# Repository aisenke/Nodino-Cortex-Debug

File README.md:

Nodino-Cortex-Debug
===================

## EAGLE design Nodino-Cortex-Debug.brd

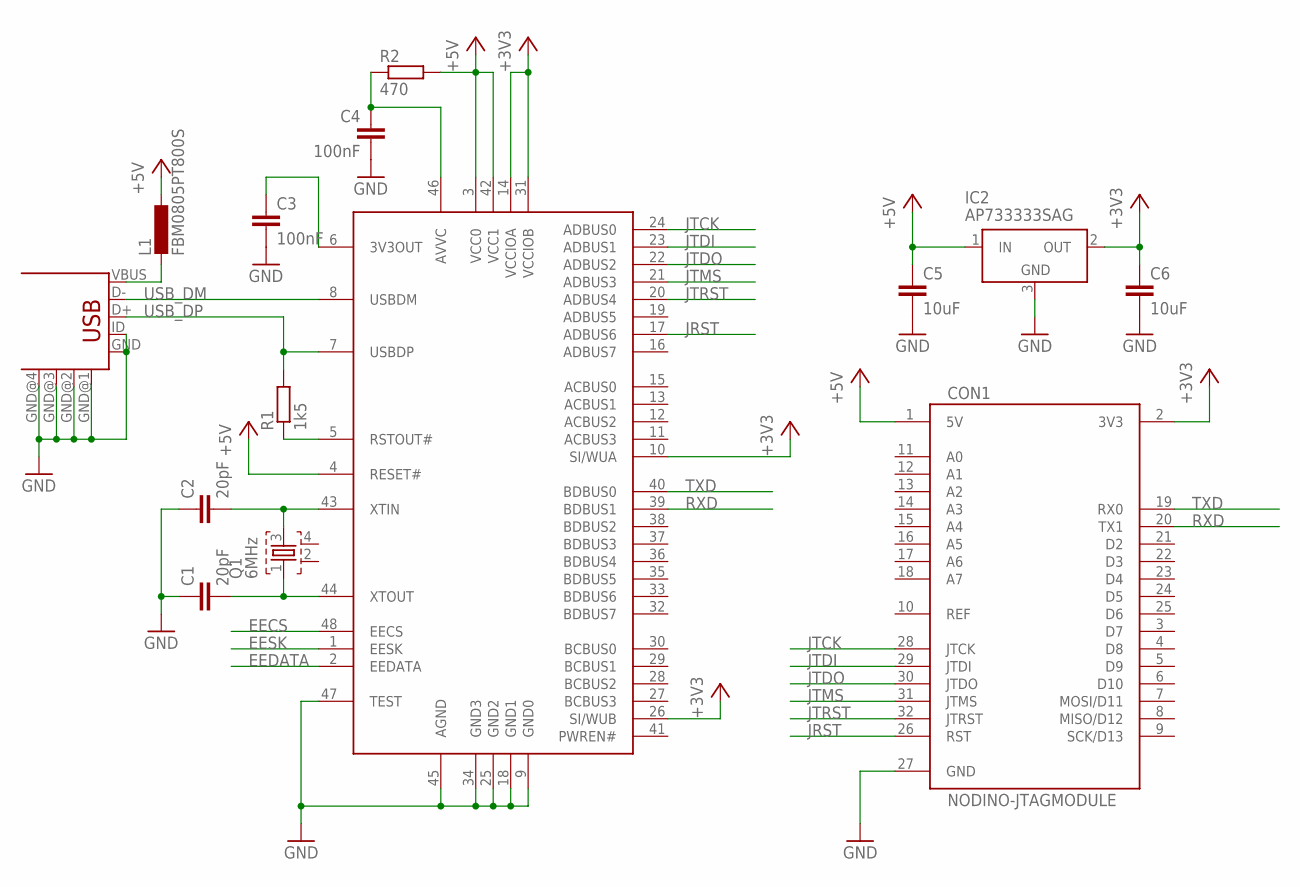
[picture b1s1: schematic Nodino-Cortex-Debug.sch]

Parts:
C1, C2: 20pF; C0603K
C3, C4: 100nF; C0603K
C5, C6: 10uF; C0603K
CON1: NODINO-JTAGMODULE; NODINO-JTAG-MOD
CON2: USB-OTG_SHIELD; USB-UAB-S1
IC1: FT2232D; LQFP48
IC2: AP733333SAG; SOT23
L1: FBM0805PT800S; L0805
Q1: 6MHz; FA-20H
R1: 1k5; R0603K
R2: 470; R0603K

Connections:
+3V3: C6.1, CON1.2 (3V3), IC1.10 (SI/WUA), IC1.14 (VCCIOA), IC1.26 (SI/WUB), IC1.31 (VCCIOB), IC2.2 (OUT)
+5V: C5.1, CON1.1 (5V), IC1.3 (VCC0), IC1.4 (RESET#), IC1.42 (VCC1), IC2.1 (IN), L1.1, R2.2
EECS: IC1.48 (EECS)
EEDATA: IC1.2 (EEDATA)
EESK: IC1.1 (EESK)
GND: C1.1, C2.1, C3.2, C4.2, C5.2, C6.2, CON1.27 (GND), CON2.GND, CON2.GND@1 (GND), CON2.GND@2 (GND), CON2.GND@3 (GND), CON2.GND@4 (GND), CON2.ID, IC1.9 (GND0), IC1.18 (GND1), IC1.25 (GND2), IC1.34 (GND3), IC1.45 (AGND), IC1.47 (TEST), IC2.3 (GND)
JRST: CON1.26 (RST), IC1.17 (ADBUS6)
JTCK: CON1.28 (JTCK), IC1.24 (ADBUS0)
JTDI: CON1.29 (JTDI), IC1.23 (ADBUS1)
JTDO: CON1.30 (JTDO), IC1.22 (ADBUS2)
JTMS: CON1.31 (JTMS), IC1.21 (ADBUS3)
JTRST: CON1.32 (JTRST), IC1.20 (ADBUS4)
unnamed: CON2.VBUS, L1.2
unnamed: IC1.5 (RSTOUT#), R1.1
unnamed: C4.1, IC1.46 (AVVC), R2.1
unnamed: C3.1, IC1.6 (3V3OUT)
unnamed: C1.2, IC1.44 (XTOUT), Q1.1
unnamed: C2.2, IC1.43 (XTIN), Q1.3
RXD: CON1.20 (TX1), IC1.39 (BDBUS1)
TXD: CON1.19 (RX0), IC1.40 (BDBUS0)
USB_DM: CON2.D-, IC1.8 (USBDM)
USB_DP: CON2.D+, IC1.7 (USBDP), R1.2

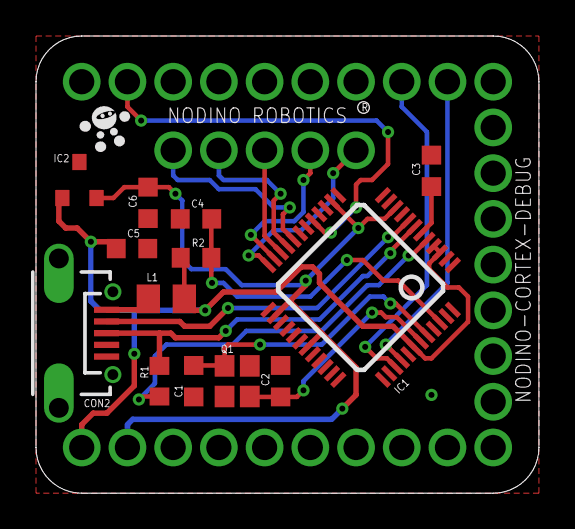
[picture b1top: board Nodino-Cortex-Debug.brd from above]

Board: 2 copper layers, 27.9 x 25.4 mm, 14 parts (0 on the bottom side), 19 nets.

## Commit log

2014-03-27 swap TXD and RXD, added filter capacitors
2014-05-11 minor fix to crystal value typo from 16MHz to 6MHz
